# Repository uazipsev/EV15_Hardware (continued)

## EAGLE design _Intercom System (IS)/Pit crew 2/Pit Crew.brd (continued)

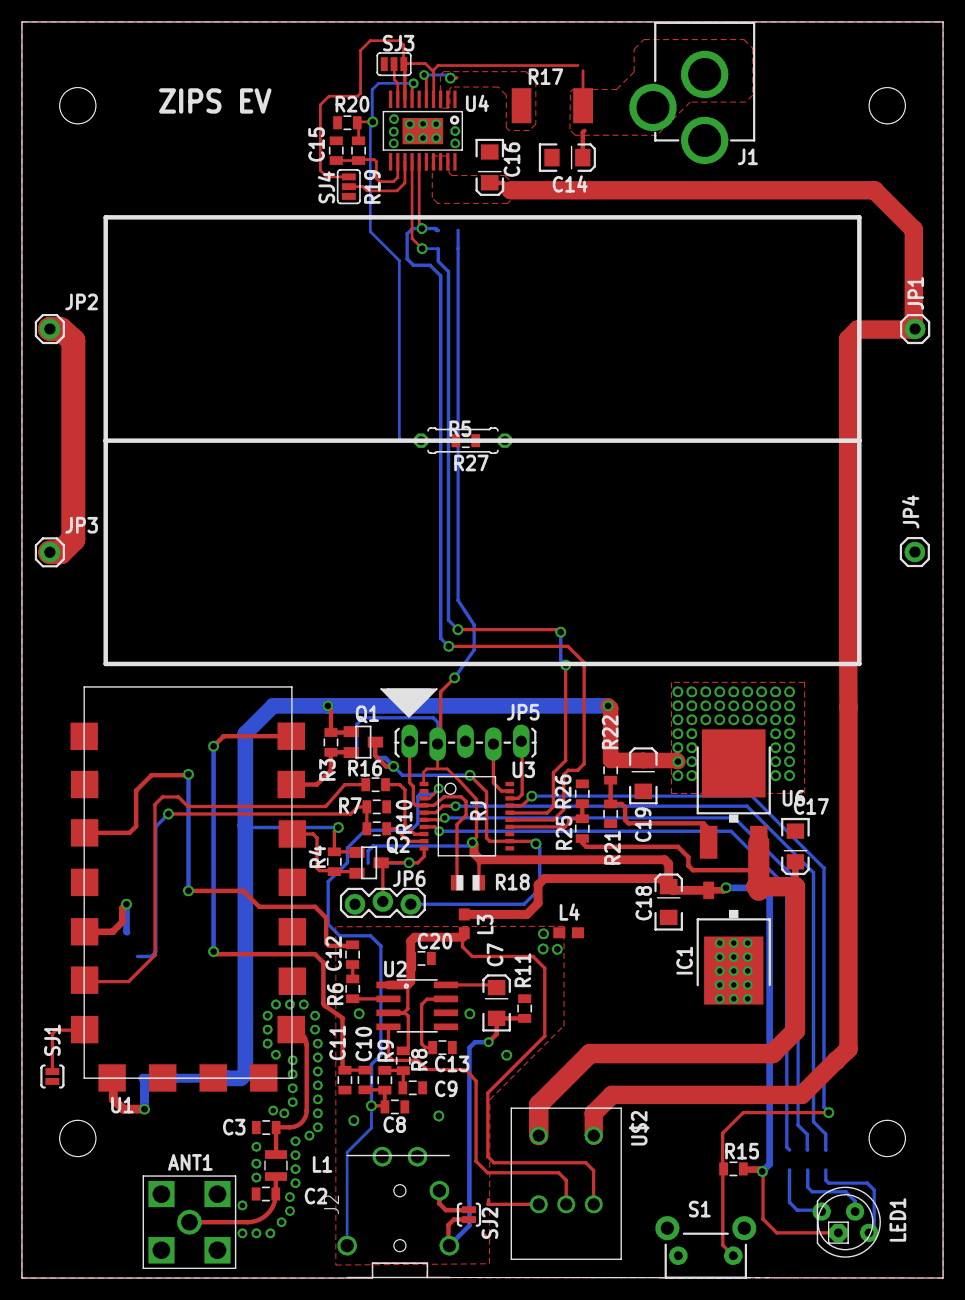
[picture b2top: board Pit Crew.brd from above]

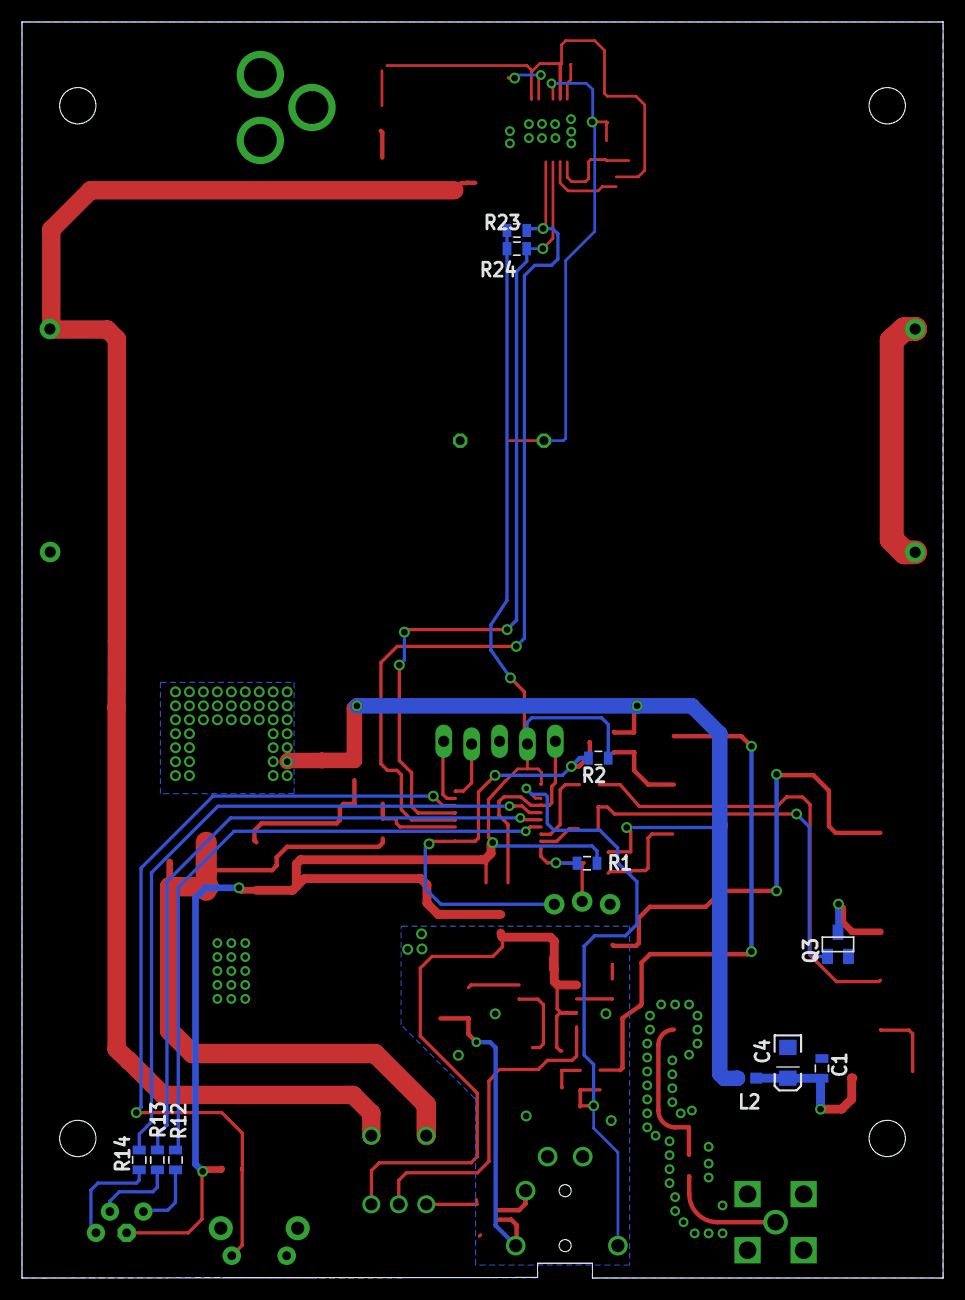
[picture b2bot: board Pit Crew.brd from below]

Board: 2 copper layers, 83.8 x 114.3 mm, 79 parts (11 on the bottom side), 52 nets.

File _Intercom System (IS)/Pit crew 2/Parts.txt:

ANT1	SMA	SMA	CONSMA002	FSAE	2	
C1	100nF	CAP0805	805	SparkFun-Passives	2	
C2	DNC	CAP0805	805	SparkFun-Passives	2	
C3	DNC	CAP0805	805	SparkFun-Passives	2	
C4	100uF	CAP_POL1206	EIA3216	SparkFun-Passives	2	
C5	0.1uf	CAP0805	805	SparkFun-Capacitors	1	
C6	0.1uf	CAP0805	805	SparkFun-Capacitors	1	
C7	10uF	10UF-TANT	EIA3216	SparkFun-Capacitors	2	
C8	470uF	CAP0805	805	SparkFun-Passives	2	
C9	1uF	CAP0805	805	SparkFun-Passives	2	
C10	100nF	CAP0805	805	SparkFun-Passives	2	
C11	100nF	CAP0805	805	SparkFun-Passives	2	
C12	470nF	CAP0805	805	SparkFun-Passives	2	
C13	1uF	CAP0805	805	SparkFun-Passives	2	
C14	10uF	10UF-TANT	EIA3216	SparkFun-Capacitors	1	
C15	0.22uF	CAP0805	805	SparkFun-Passives	1	
C16	1uF	10UF-TANT	EIA3216	SparkFun-Capacitors	1	
C17	10uF	10UF-TANT	EIA3216	SparkFun-Capacitors	1	
C18	10uF	10UF-TANT	EIA3216	SparkFun-Capacitors	1	
C19	10uF	10UF-TANT	EIA3216	SparkFun-Capacitors	1	
C20	0.1uf	CAP0805	805	SparkFun-Passives	2	
IC1	7805	7806DT	TO252	adafruit	1	
J1	POWER_JACKPTH	POWER_JACKPTH	POWER_JACK_PTH	SparkFun-Connectors	1	
JP1	M01PTH	M01PTH	1X01	SparkFun-Connectors	1	
JP2	M01PTH	M01PTH	1X01	SparkFun-Connectors	1	
JP3	M01PTH	M01PTH	1X01	SparkFun-Connectors	1	
JP4	M01PTH	M01PTH	1X01	SparkFun-Connectors	1	
JP5		M05LOCK_LONGPADS	1X05_LOCK_LONGPADS	SparkFun-Connectors	1	
JP6		M03LOCK	1X03_LOCK	SparkFun-Connectors	2	
L1	0	INDUCTOR1007	1007	SparkFun-Passives	2	
L2	BLM18EG221TN1D	INDUCTOR0603	603	SparkFun-Passives	2	
L3	BLM18HG102SN1D	INDUCTOR0603	603	SparkFun-Passives	2	
L4	BLM18HG102SN1D	INDUCTOR0603	603	SparkFun-Passives	2	
LED1	RGBLED_CA-5MM	RGBLED_CA-5MM	LED5MMRGB	adafruit	1	
Q1	BSS123	MOSFET-NCHANNELBSS123LT1G	SOT23	SparkFun-DiscreteSemi	2	
Q2	BSS123	MOSFET-NCHANNELBSS123LT1G	SOT23	SparkFun-DiscreteSemi	2	
Q3	BSS123	MOSFET-NCHANNELBSS123LT1G	SOT23	SparkFun-DiscreteSemi	2	
R1	10k	RESISTOR0805-RES	805	SparkFun-Passives	2	
R2	10k	RESISTOR0805-RES	805	SparkFun-Passives	2	
R3	10k	RESISTOR0805-RES	805	SparkFun-Passives	2	
R4	10k	RESISTOR0805-RES	805	SparkFun-Passives	2	
R5		RESISTOR0805-RES	805	SparkFun-Passives	1	
R6	68k	RESISTOR0805-RES	805	SparkFun-Passives	2	
R7	10k	RESISTOR0805-RES	805	SparkFun-Passives	2	
R8	1k	RESISTOR0805-RES	805	SparkFun-Passives	2	
R9	2.2k	RESISTOR0805-RES	805	SparkFun-Passives	2	
R10	1k	RESISTOR0805-RES	805	SparkFun-Passives	2	
R11	1k	RESISTOR0805-RES	805	SparkFun-Passives	2	
R12		RESISTOR0805-RES	805	SparkFun-Passives	1	
R13		RESISTOR0805-RES	805	SparkFun-Passives	1	
R14		RESISTOR0805-RES	805	SparkFun-Passives	1	
R15	10k	RESISTOR0805-RES	805	SparkFun-Passives	1	
R16	1k	RESISTOR0805-RES	805	SparkFun-Passives	1	
R17	0.2	RESISTOR2512	R2512	SparkFun-Passives	1	
R18	10k	R-US_R0805	R0805	adafruit	1	
R19	10k	RESISTOR0805-RES	805	SparkFun-Passives	1	
R20	10k	RESISTOR0805-RES	805	SparkFun-Passives	1	
R21	620	RESISTOR0805-RES	805	SparkFun-Passives	1	
R22	240	RESISTOR0805-RES	805	SparkFun-Passives	1	
R23	10k	RESISTOR0805-RES	805	SparkFun-Passives	1	
R24	10k	RESISTOR0805-RES	805	SparkFun-Passives	1	
R25	12k	RESISTOR0805-RES	805	SparkFun-Passives	1	
R26	20k	RESISTOR0805-RES	805	SparkFun-Passives	1	
R27		R-US_0207/7	0207/7	adafruit	1	
S1	NO	SWITCH-MOMENTARY-2SIDE_EZ	TACTILE-PTH-SIDEEZ	SparkFun-Electromechanical	1	
SJ1	NO	SOLDERJUMPERNO	SJ_2S-NO	SparkFun-Passives	2	
SJ2	SOLDERJUMPERNO	SJ_2S-NO	SparkFun-Passives	2		
SJ3	SOLDERJUMPER_2WAYS	SJ_3	SparkFun-Passives	1		
SJ4	SOLDERJUMPER_2WAYS	SJ_3	SparkFun-Passives	1		
U$1	AUDIO-JACK3	AUDIO-JACK3	AUDIO-JACK-TRRS-SMD	SparkFun-Connectors	2	
U$2	PTR901-2015K-B103	PTR901-2015K-B103	PTR901-2015K-B103	FSAE	Eletric	2
U1	SR-FRS-1W	SR-FRS-1W	SR-FRS-1W	FSAE	Eletric	2
U2	LM4875MX	LM4875MX	SO-8	FSAE	Eletric	2
U3	PIC16F721	PIC16F721	SSOP-20	FSAE	Eletric	1
U4	BQ24005PWP	BQ24005PWP	HTSSOP-20	FSAE	Eletric	1
U6	AZ1117CD-ADJTRG1	V_REG_317DPACK	V-REG_DPACK	SparkFun-PowerIC	1

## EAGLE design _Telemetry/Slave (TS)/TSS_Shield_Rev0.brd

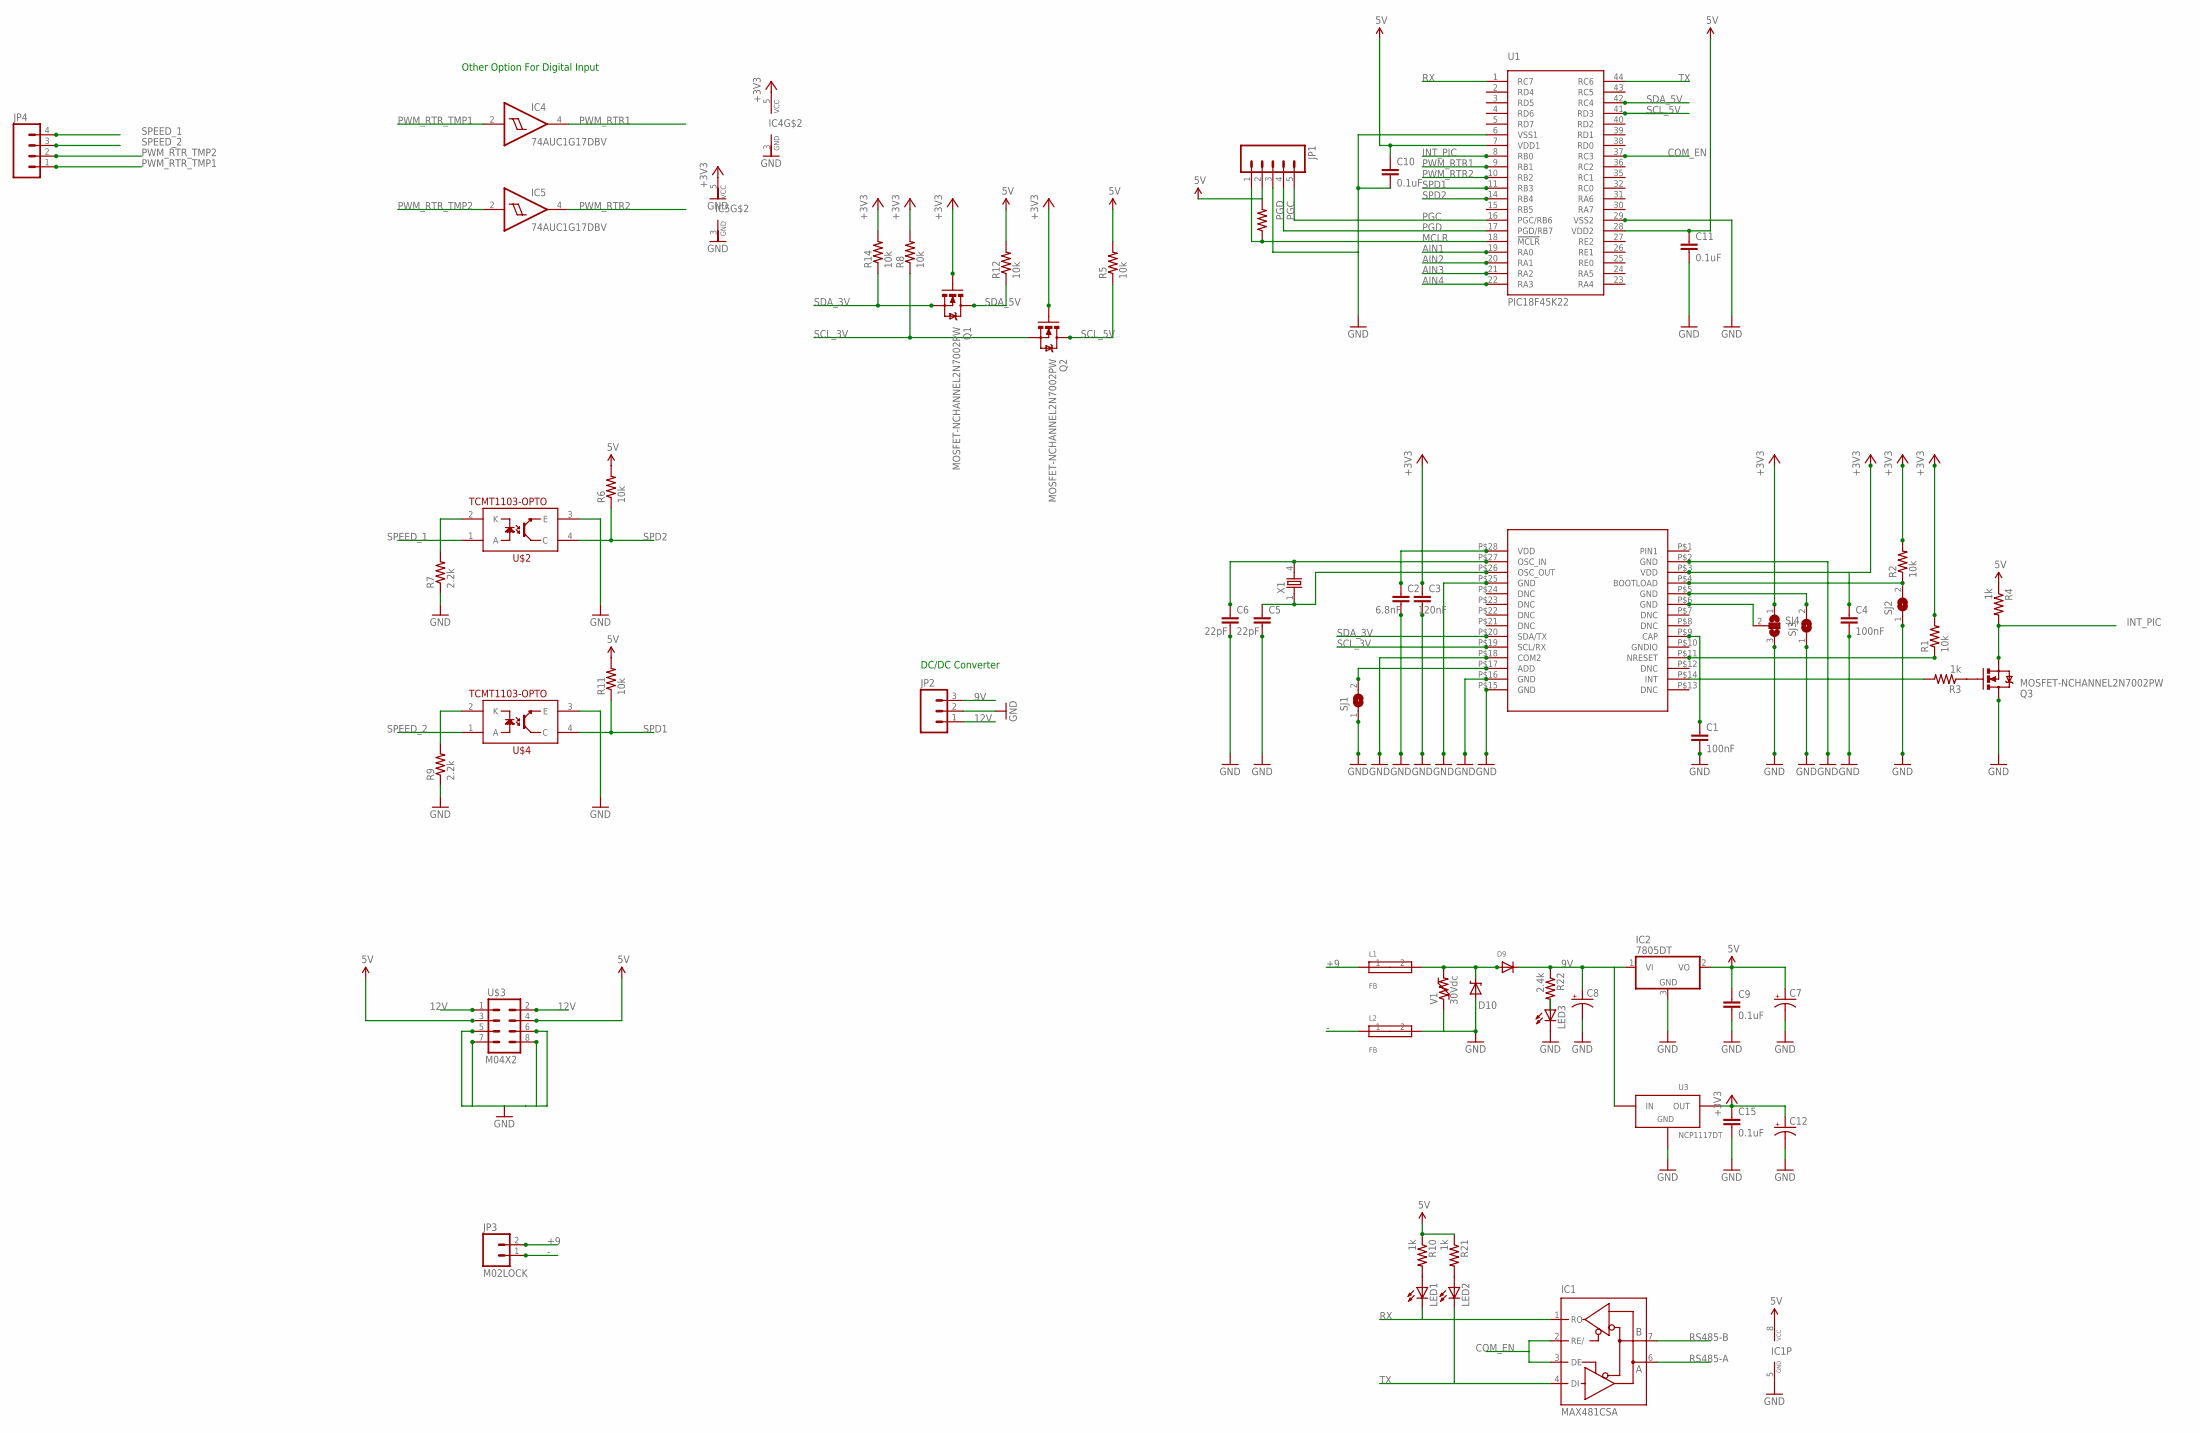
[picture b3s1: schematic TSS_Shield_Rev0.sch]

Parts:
C1, C4: 100nF; 0805
C2: 6.8nF; 0805
C3: 120nF; 0805
C5, C6: 22pF; 0805
C7, C12: CPOL-USCT3528; CT3528
C8: CAP_POL7343; EIA7343
C9, C10, C11, C15: 0.1uF; 0805
D9: DIODESOD-123; SOD-123
D10: MM5Z30; SOD-523F
IC1: MAX481CSA; SO08
IC2: 7805DT; TO252
IC4, IC5: 74AUC1G17DBV; SOT23-5
JP1: M05LOCK; 1X05_LOCK
JP2: M03PTH; 1X03
JP3: M02LOCK; 1X02_LOCK
JP4: M04LOCK; 1X04_LOCK
L1, L2: FB; 0603
LED1, LED2, LED3: LEDCHIP-LED0805; CHIP-LED0805
Q1, Q2, Q3: MOSFET-NCHANNEL2N7002PW; SOT323
R1, R2, R5, R6, R8, R11, R12, R13, R14: 10k; 0805
R3, R4, R10, R21: 1k; 0805
R7, R9: 2.2k; 0805
R22: 2.4k; 0805
SJ1, SJ2, SJ3: SJ
SJ4: SJ2W; SJ_2
U1: PIC18F45K22; TQFP-44
U2: BOSCH_IMUSURFACEMOUNT; LGA_28
U3: NCP1117DT; DPAK
U$2, U$4: TCMT1103-OPTO; SSOP-4
U$3: M04X2; 2X4
V1: 30Vdc; 0603
X1: 86SMX

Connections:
5V: C7.+, C9.1, C10.1, C11.1, IC1.8 (VCC), IC2.2 (VO), JP1.2, R4.1, R5.2, R6.2, R10.1, R11.2, R12.2, R13.2, R21.1, U1.7 (VDD1), U1.28 (VDD2), U$3.3, U$3.4
9V: C8.A (+), D9.C, IC2.1 (VI), JP2.3, R22.1, U3.3 (IN)
12V: JP2.1, U$3.1, U$3.2
+3V3: C2.1, C3.1, C4.1, C12.+, C15.1, IC4.5 (VCC), IC5.5 (VCC), Q1.1 (G), Q2.1 (G), R1.2, R2.2, R8.2, R14.2, SJ4.1, U2.P$3 (VDD), U2.P$28 (VDD), U3.2 (OUT)
+9: JP3.2, L1.1
-: JP3.1, L2.1
AIN1: U1.19 (RA0)
AIN2: U1.20 (RA1)
AIN3: U1.21 (RA2)
AIN4: U1.22 (RA3)
COM_EN: IC1.2 (RE/), IC1.3 (DE), U1.37 (RC3)
GHT: D9.A, D10.C, L1.2, V1.2
GND: C1.2, C2.2, C3.2, C4.2, C5.2, C6.2, C7.-, C8.C (-), C9.2, C10.2, C11.2, C12.-, C15.2, D10.A, IC1.5 (GND), IC2.3 (GND), IC4.3 (GND), IC5.3 (GND), JP1.3, JP2.2, L2.2, LED3.C, Q3.3 (D), R7.1, R9.1, SJ1.1, SJ2.1, SJ3.1, SJ4.3, U1.6 (VSS1), U1.29 (VSS2), U2.P$2 (GND), U2.P$15 (GND), U2.P$16 (GND), U2.P$18 (COM2), U2.P$25 (GND), U3.1 (GND), U$2.3 (E), U$3.5, U$3.6, U$3.7, U$3.8, U$4.3 (E), V1.1
INT_PIC: Q3.2 (S), R4.2, U1.8 (RB0)
MCLR: JP1.1, R13.1, U1.18 (!MCLR)
unnamed: SJ3.2, U2.P$5 (GND)
unnamed: R2.1, SJ2.2, U2.P$4 (BOOTLOAD)
unnamed: SJ4.2, U2.P$6 (GND)
unnamed: LED3.A, R22.2
unnamed: LED1.A, R10.2
unnamed: LED2.A, R21.2
unnamed: C6.1, U2.P$27 (OSC_IN), X1.4 (2)
unnamed: C5.1, U2.P$26 (OSC_OUT), X1.1
unnamed: R7.2, U$2.2 (K)
unnamed: SJ1.2, U2.P$17 (ADD)
unnamed: R9.2, U$4.2 (K)
unnamed: R3.2, U2.P$14 (INT)
unnamed: C1.1, U2.P$9 (CAP)
unnamed: R1.1, U2.P$11 (NRESET)
unnamed: Q3.1 (G), R3.1
PGC: JP1.5, U1.16 (PGC/RB6)
PGD: JP1.4, U1.17 (PGD/RB7)
PWM_RTR1: IC4.4 (O), U1.9 (RB1)
PWM_RTR2: IC5.4 (O), U1.10 (RB2)
PWM_RTR_TMP1: IC4.2 (I), JP4.1
PWM_RTR_TMP2: IC5.2 (I), JP4.2
RS485-A: IC1.6 (A)
RS485-B: IC1.7 (B)
RX: IC1.1 (RO), LED1.C, U1.1 (RC7)
SCL_3V: Q2.2 (S), R8.1, U2.P$19 (SCL/RX)
SCL_5V: Q2.3 (D), R5.1, U1.41 (RD3)
SDA_3V: Q1.2 (S), R14.1, U2.P$20 (SDA/TX)
SDA_5V: Q1.3 (D), R12.1, U1.42 (RC4)
SPD1: R11.1, U1.11 (RB3), U$4.4 (C)
SPD2: R6.1, U1.14 (RB4), U$2.4 (C)
SPEED_1: JP4.4, U$2.1 (A)
SPEED_2: JP4.3, U$4.1 (A)
TX: IC1.4 (DI), LED2.C, U1.44 (RC6)

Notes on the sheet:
DC/DC Converter
Other Option For Digital Input

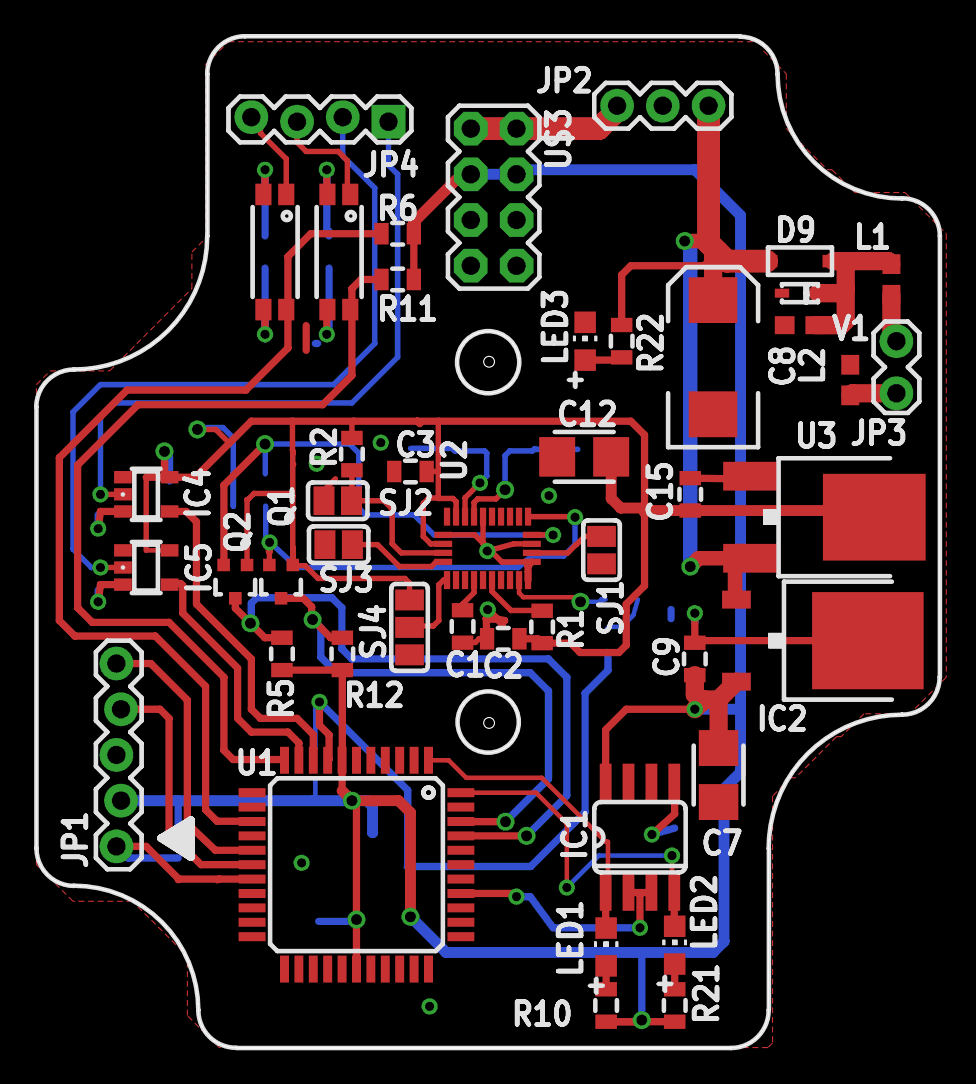
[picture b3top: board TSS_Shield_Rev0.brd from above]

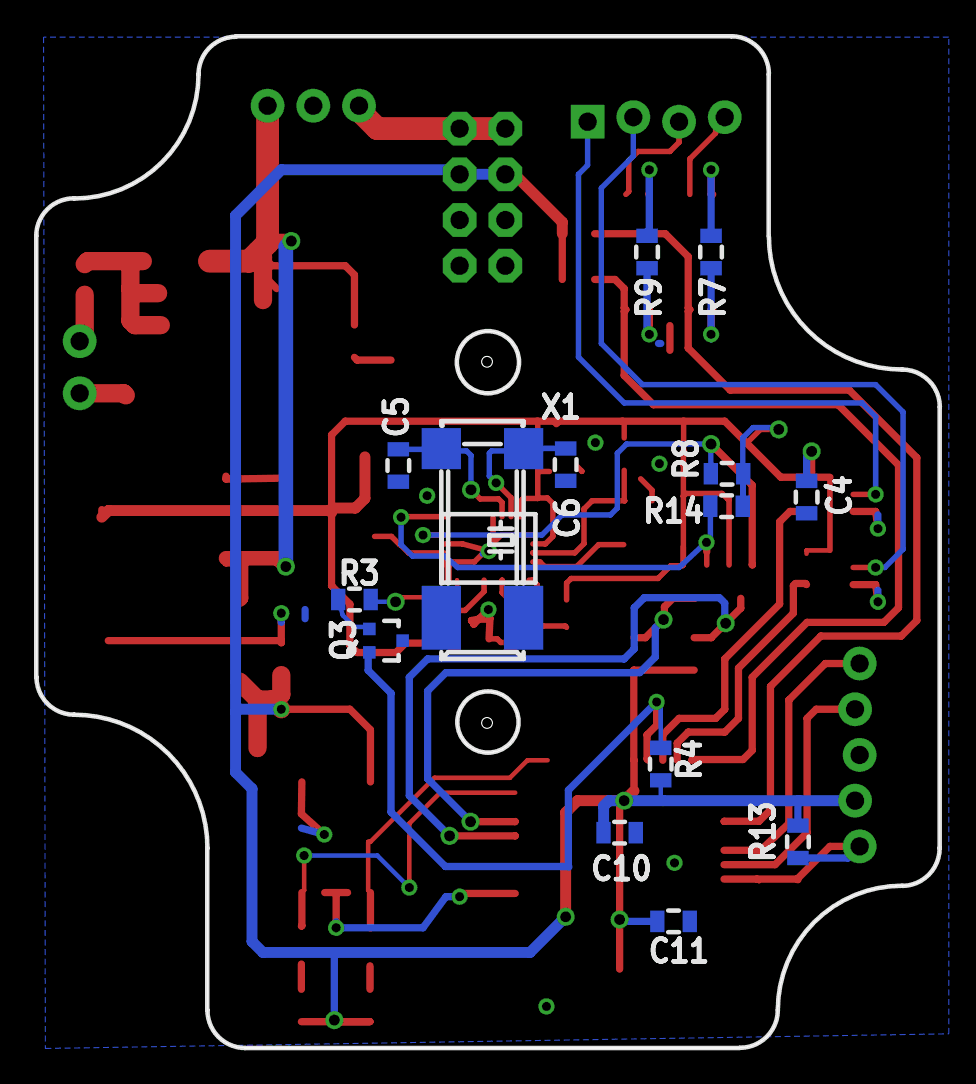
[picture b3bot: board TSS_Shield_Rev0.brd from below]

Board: 2 copper layers, 50.2 x 56.2 mm, 59 parts (14 on the bottom side), 42 nets.

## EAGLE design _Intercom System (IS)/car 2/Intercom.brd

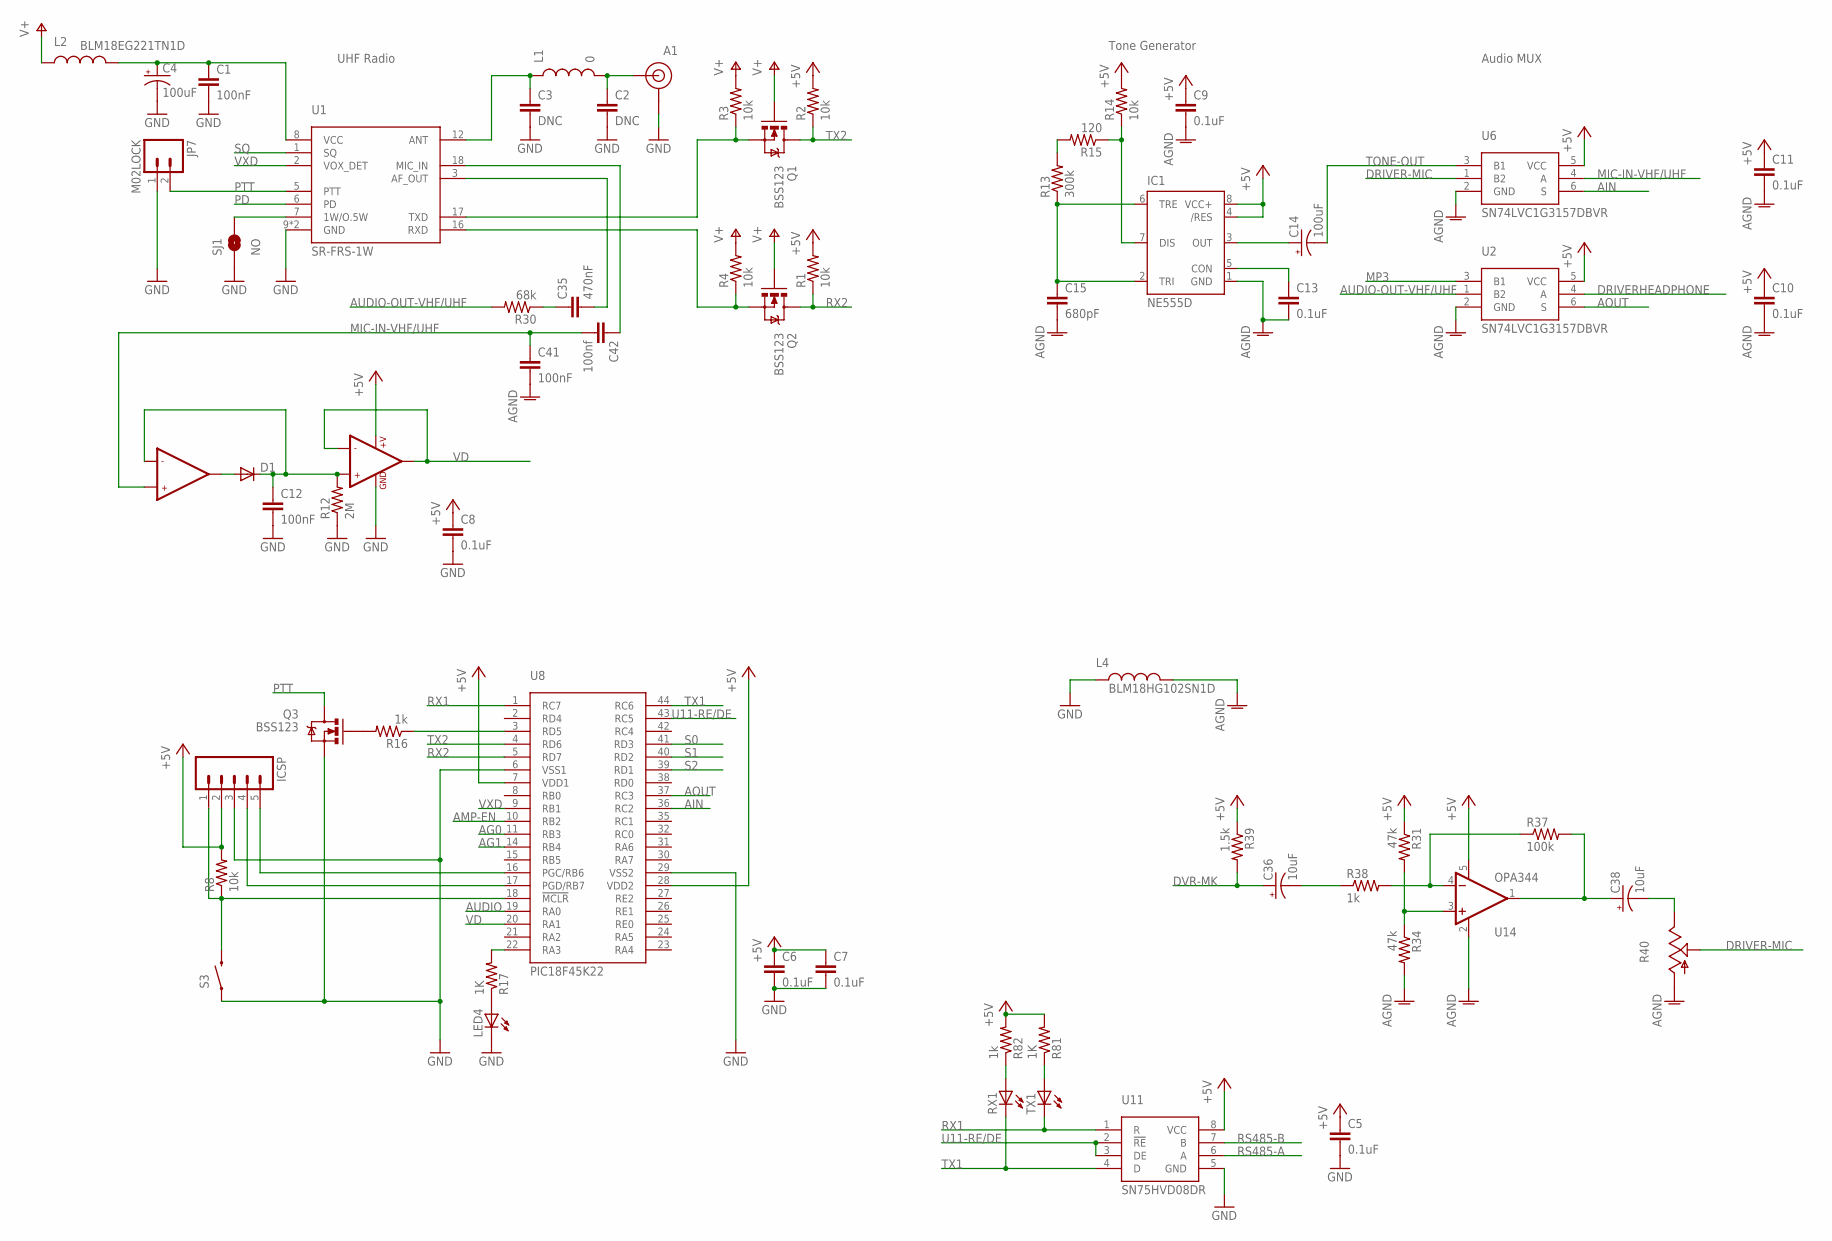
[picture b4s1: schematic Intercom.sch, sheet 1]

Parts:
A1: CONSMA003.062
C1, C12, C41: 100nF; 0805
C2, C3: DNC; 0805
C4: 100uF; EIA3216
C5, C6, C7, C8, C9, C10, C11, C13: 0.1uF; 0805
C14: 100uF; EIA3528-KIT
C15: 680pF; 0805
C35: 470nF; 0805
C36, C38: 10uF; EIA3216
C42: 100nf; 0805
D1: DIODESOD; SOD-323
IC1: NE555D; SO08
ICSP: M05LOCK_LONGPADS; 1X05_LOCK_LONGPADS
JP7: M02LOCK; 1X02_LOCK
L1: 0; 1007
L2: BLM18EG221TN1D; 0603
L4: BLM18HG102SN1D; 0805
LED4: LEDCHIPLED_0805; CHIPLED_0805
Q1, Q2, Q3: BSS123; SOT23
R1, R2, R3, R4, R8, R14: 10k; 0805
R12: 2M; 0805
R13: 300k; 0805
R15: 120; 0805
R16, R38: 1k; 0805
R17, R81: 1K; R0805
R30: 68k; 0805
R31, R34: 47k; 0805
R37: 100k; 0805
R39: 1.5k; 0805
R40: TRIM_US-CA6H; CA6H
R82: 1k; R0805
RX1: LEDCHIPLED_0805; CHIPLED_0805
S3: SWITCH-MOMENTARY-2SIDE_EZ; TACTILE-PTH-SIDEEZ
SJ1: NO; SJ_2S-NO
TX1: LEDCHIPLED_0805; CHIPLED_0805
U1: SR-FRS-1W
U2, U6: SN74LVC1G3157DBVR; SOT23-6
U8: PIC18F45K22; TQFP-44
U11: SN75HVD08DR; SO-8
U12: LMV358; SO08
U14: OPA344; SOT23-5

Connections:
+5V: C5.1, C6.1, C7.1, C8.1, C9.1, C10.1, C11.1, IC1.4 (/RES), IC1.8 (VCC+), ICSP.2, R1.2, R2.2, R8.2, R14.2, R31.1, R39.1, R81.2, R82.2, U2.5 (VCC), U6.5 (VCC), U8.7 (VDD1), U8.28 (VDD2), U11.8 (VCC), U12.8 (+V), U14.5 (V+); also elsewhere on the board
AG0: U8.11 (RB3)
AG1: U8.14 (RB4)
AGND: C9.2, C10.2, C11.2, C13.2, C15.2, C41.2, IC1.1 (GND), L4.2, R34.2, R40.A, U2.2 (GND), U6.2 (GND), U14.2 (V-); also elsewhere on the board
AIN: U6.6 (S), U8.36 (RC2)
AMP-EN: U8.10 (RB2)
AOUT: U2.6 (S), U8.37 (RC3)
AUDIO: U8.19 (RA0)
AUDIO-OUT-VHF/UHF: R30.2, U2.1 (B2)
DRIVER-MIC: R40.S, U6.1 (B2)
DRIVERHEADPHONE: U2.4 (A)
DVR-MK: C36.A (+), R39.2; also elsewhere on the board
GND: A1.G (GND), A1.G1 (GND), A1.G2 (GND), A1.G3 (GND), C1.2, C2.2, C3.2, C4.C (-), C5.2, C6.2, C7.2, C8.2, C12.2, ICSP.3, JP7.1, L4.1, LED4.C, Q3.2 (S), R12.1, S3.1, SJ1.1, U1.9 (GND), U1.10 (GND), U8.6 (VSS1), U8.29 (VSS2), U11.5 (GND), U12.4 (GND); also elsewhere on the board
MIC-IN-VHF/UHF: C41.1, C42.2, U6.4 (A), U12.5 (+IN2)
MP3: U2.3 (B1); also elsewhere on the board
unnamed: C3.1, L1.1, U1.12 (ANT)
unnamed: A1.S (SIGNAL), C2.1, L1.2
unnamed: C1.1, C4.A (+), L2.2, U1.8 (VCC)
unnamed: SJ1.2, U1.7 (1W/O.5W)
unnamed: D1.2 (A), U12.7 (OUT2)
unnamed: C15.1, IC1.2 (TRI), IC1.6 (TRE), R13.1
unnamed: Q2.2 (S), R4.1, U1.16 (RXD)
unnamed: Q1.2 (S), R3.1, U1.17 (TXD)
unnamed: C35.2, U1.3 (AF_OUT)
unnamed: R31.2, R34.1, U14.3 (+IN)
unnamed: C35.1, R30.1
unnamed: R16.1, U8.3 (RD5)
unnamed: C38.C (-), R40.E
unnamed: C12.1, D1.1 (C), R12.2, U12.3 (+IN1), U12.6 (-IN2)
unnamed: IC1.7 (DIS), R14.1, R15.1
unnamed: R13.2, R15.2
unnamed: C13.1, IC1.5 (CON)
unnamed: Q3.1 (G), R16.2
unnamed: C14.A (+), IC1.3 (OUT)
unnamed: LED4.A, R17.1
unnamed: R17.2, U8.22 (RA3)
unnamed: C38.A (+), R37.2, U14.1 (OUT)
unnamed: R37.1, R38.2, U14.4 (-IN)
unnamed: C36.C (-), R38.1
unnamed: ICSP.4, U8.17 (PGD/RB7)
unnamed: ICSP.5, U8.16 (PGC/RB6)
unnamed: ICSP.1, R8.1, S3.2, U8.18 (!MCLR)
unnamed: C42.1, U1.18 (MIC_IN)
unnamed: R81.1, TX1.A
unnamed: R82.1, RX1.A
PD: U1.6 (PD)
PTT: JP7.2, Q3.3 (D), U1.5 (PTT)
RS485-A: U11.6 (A); also elsewhere on the board
RS485-B: U11.7 (B); also elsewhere on the board
RX1: TX1.C, U8.1 (RC7), U11.1 (R)
RX2: Q2.3 (D), R1.1, U8.5 (RD7)
S0: U8.41 (RD3); also elsewhere on the board
S1: U8.40 (RD2); also elsewhere on the board
S2: U8.39 (RD1); also elsewhere on the board
SQ: U1.1 (SQ)
TONE-OUT: C14.C (-), U6.3 (B1)
TX1: RX1.C, U8.44 (RC6), U11.4 (D)
TX2: Q1.3 (D), R2.1, U8.4 (RD6)
U11-RE/DE: U8.43 (RC5), U11.2 (!RE), U11.3 (DE)
V+: L2.1, Q1.1 (G), Q2.1 (G), R3.2, R4.2; also elsewhere on the board
VD: U8.20 (RA1), U12.1 (OUT1), U12.2 (-IN1)
VXD: U1.2 (VOX_DET), U8.9 (RB1)

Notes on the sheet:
UHF Radio
Tone Generator
Audio MUX

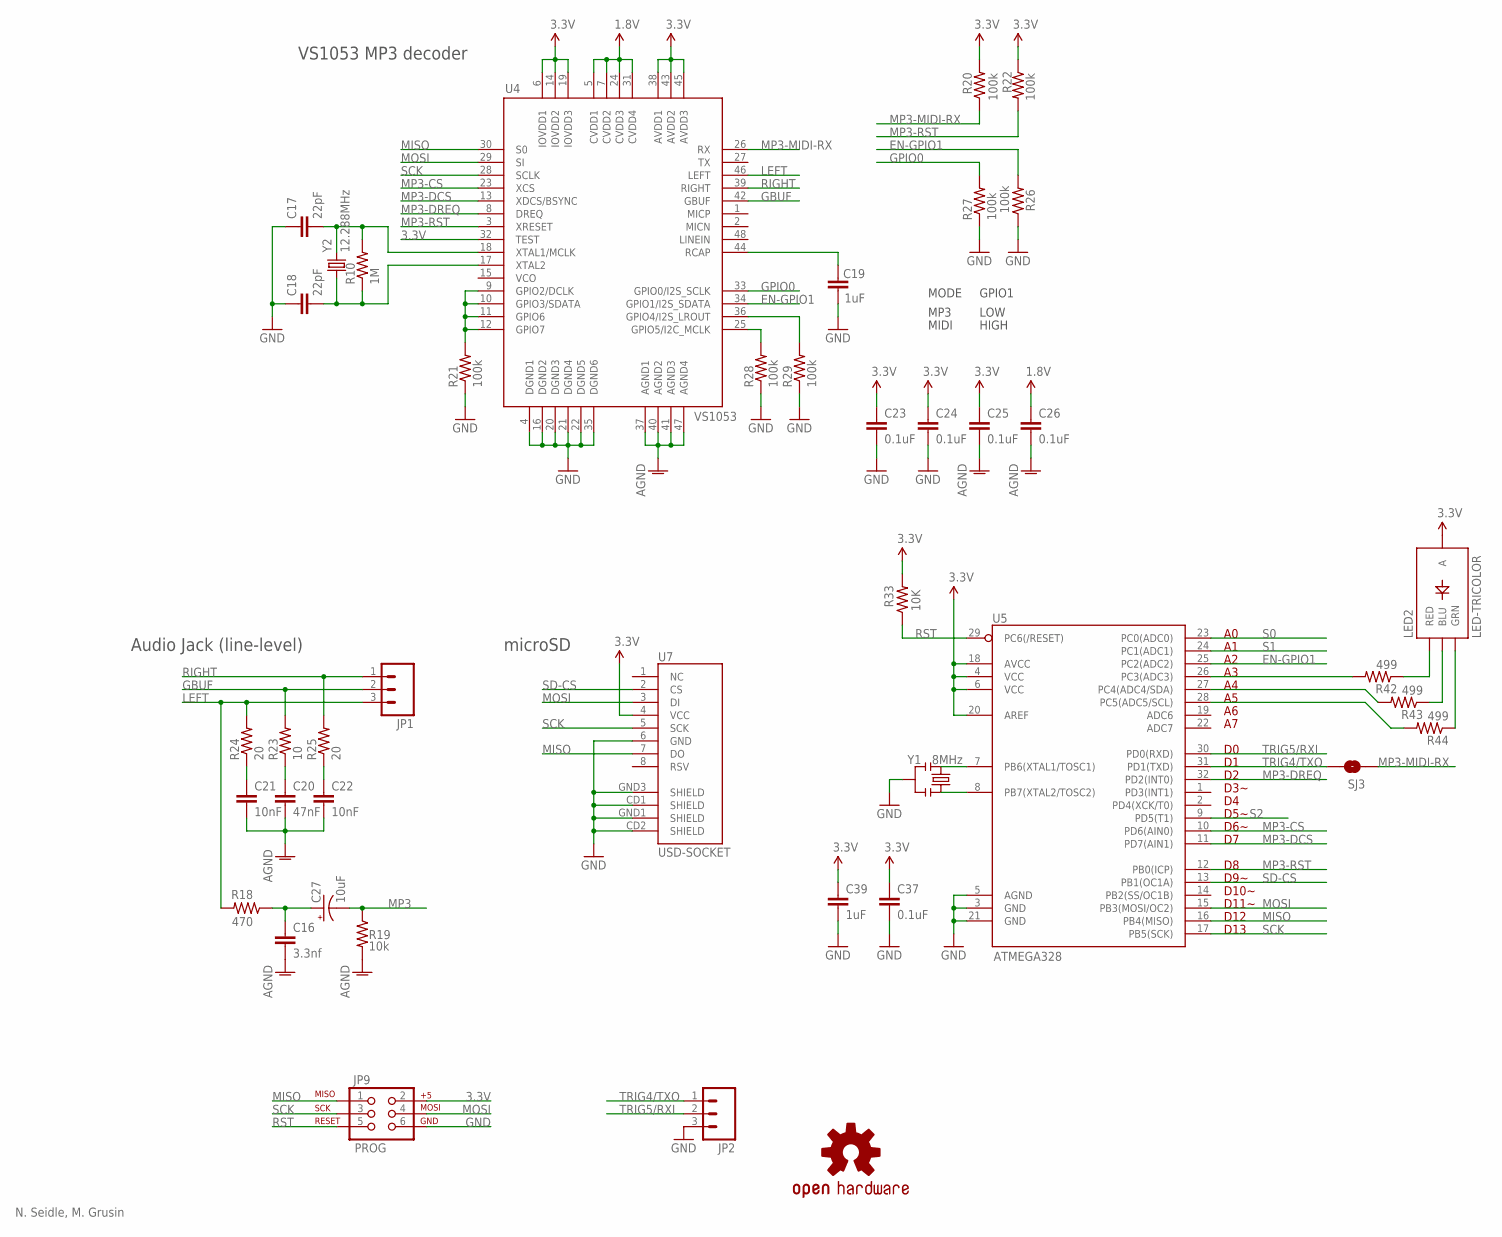
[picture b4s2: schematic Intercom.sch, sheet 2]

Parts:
C16: 3.3nf; 0805
C17, C18: 22pF; 0805
C19, C39: 1uF; 0805
C20: 47nF; 0805
C21, C22: 10nF; 0805
C23, C24, C25, C26, C37: 0.1uF; 0805
C27: 10uF; CT6032
JP1: M03PTH; 1X03
JP2: M03LOCK_LONGPADS; 1X03_LOCK_LONGPADS
JP9: PROG; 2X3-NS
LED2: LED-TRICOLOR; LED-TRICOLOR-SMD
R10: 1M; 0805
R18: 470; 0805
R19: 10k; 0805
R20, R21, R22, R26, R27, R28, R29: 100k; 0805
R23: 10; 0805
R24, R25: 20; 0805
R33: 10K; 0805
R42, R43, R44: 499; 0805
SJ3: SOLDERJUMPERNO; SJ_2S-NO
U4: VS1053; LQFP-48
U5: ATMEGA328; TQFP32-08
U7: USD-SOCKET; MICRO-SD-SOCKET-PP
U$5: OSHW-LOGOM; OSHW-LOGO-M
Y1: 8MHz; RESONATOR-SMD
Y2: 12.288MHz; CRYSTAL-SMD-5X3

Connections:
1.8V: C26.1, U4.5 (CVDD1), U4.7 (CVDD2), U4.24 (CVDD3), U4.31 (CVDD4); also elsewhere on the board
3.3V: C23.1, C24.1, C25.1, C37.1, C39.1, JP9.2, LED2.A, R20.2, R22.1, R33.2, U4.6 (IOVDD1), U4.14 (IOVDD2), U4.19 (IOVDD3), U4.32 (TEST), U4.38 (AVDD1), U4.43 (AVDD2), U4.45 (AVDD3), U5.4 (VCC), U5.6 (VCC), U5.18 (AVCC), U5.20 (AREF), U7.4 (VCC); also elsewhere on the board
AGND: C16.2, C20.2, C21.2, C22.2, C25.2, C26.2, R19.2, U4.37 (AGND1), U4.40 (AGND2), U4.41 (AGND3), U4.47 (AGND4); also elsewhere on the board
EN-GPIO1: R26.2, U4.34 (GPIO1/I2S_SDATA), U5.25 (PC2(ADC2))
G1: R21.2, U4.9 (GPIO2/DCLK), U4.10 (GPIO3/SDATA), U4.11 (GPIO6), U4.12 (GPIO7)
G2: R28.2, U4.25 (GPIO5/I2C_MCLK)
GBUF: JP1.2, R23.2, U4.42 (GBUF)
GND: C17.1, C18.1, C19.1, C23.2, C24.2, C37.2, C39.2, JP2.3, JP9.6, R21.1, R26.1, R27.1, R28.1, R29.1, U4.4 (DGND1), U4.16 (DGND2), U4.20 (DGND3), U4.21 (DGND4), U4.22 (DGND5), U4.35 (DGND6), U5.3 (GND), U5.5 (AGND), U5.21 (GND), U7.6 (GND), U7.CD1 (SHIELD), U7.CD2 (SHIELD), U7.GND1 (SHIELD), U7.GND3 (SHIELD), Y1.2; also elsewhere on the board
GPIO0: R27.2, U4.33 (GPIO0/I2S_SCLK)
LEFT: JP1.3, R18.2, R24.2, U4.46 (LEFT)
MISO: JP9.1, U4.30 (S0), U5.16 (PB4(MISO)), U7.7 (DO)
MOSI: JP9.4, U4.29 (SI), U5.15 (PB3(MOSI/OC2)), U7.3 (DI)
MP3: C27.-, R19.1; also elsewhere on the board
MP3-CS: U4.23 (XCS), U5.10 (PD6(AIN0))
MP3-DCS: U4.13 (XDCS/BSYNC), U5.11 (PD7(AIN1))
MP3-DREQ: U4.8 (DREQ), U5.32 (PD2(INT0))
MP3-MIDI-RX: R20.1, SJ3.1, U4.26 (RX)
MP3-RST: R22.2, U4.3 (XRESET), U5.12 (PB0(ICP))
unnamed: C17.2, R10.2, U4.18 (XTAL1/MCLK), Y2.3 (2)
unnamed: C18.2, R10.1, U4.17 (XTAL2), Y2.1
unnamed: C16.1, C27.+, R18.1
unnamed: C19.2, U4.44 (RCAP)
unnamed: C22.1, R25.1
unnamed: C21.1, R24.1
unnamed: C20.1, R23.1
unnamed: U5.7 (PB6(XTAL1/TOSC1)), Y1.1
unnamed: U5.8 (PB7(XTAL2/TOSC2)), Y1.3
unnamed: LED2.R (RED), R42.1
unnamed: LED2.B (BLU), R43.1
unnamed: LED2.G (GRN), R44.1
unnamed: R42.2, U5.26 (PC3(ADC3))
unnamed: R43.2, U5.27 (PC4(ADC4/SDA))
unnamed: R44.2, U5.28 (PC5(ADC5/SCL))
unnamed: R29.2, U4.36 (GPIO4/I2S_LROUT)
RIGHT: JP1.1, R25.2, U4.39 (RIGHT)
RST: JP9.5, R33.1, U5.29 (PC6(/RESET))
S0: U5.23 (PC0(ADC0)); also elsewhere on the board
S1: U5.24 (PC1(ADC1)); also elsewhere on the board
S2: U5.9 (PD5(T1)); also elsewhere on the board
SCK: JP9.3, U4.28 (SCLK), U5.17 (PB5(SCK)), U7.5 (SCK)
SD-CS: U5.13 (PB1(OC1A)), U7.2 (CS)
TRIG4/TXO: JP2.1, SJ3.2, U5.31 (PD1(TXD))
TRIG5/RXI: JP2.2, U5.30 (PD0(RXD))

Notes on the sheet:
N. Seidle, M. Grusin
microSD
Audio Jack (line-level)
VS1053 MP3 decoder
GPIO1
LOW
HIGH
MODE
MP3
MIDI
D3~
D5~
D6~
D9~
D10~
D11~
D12
D13

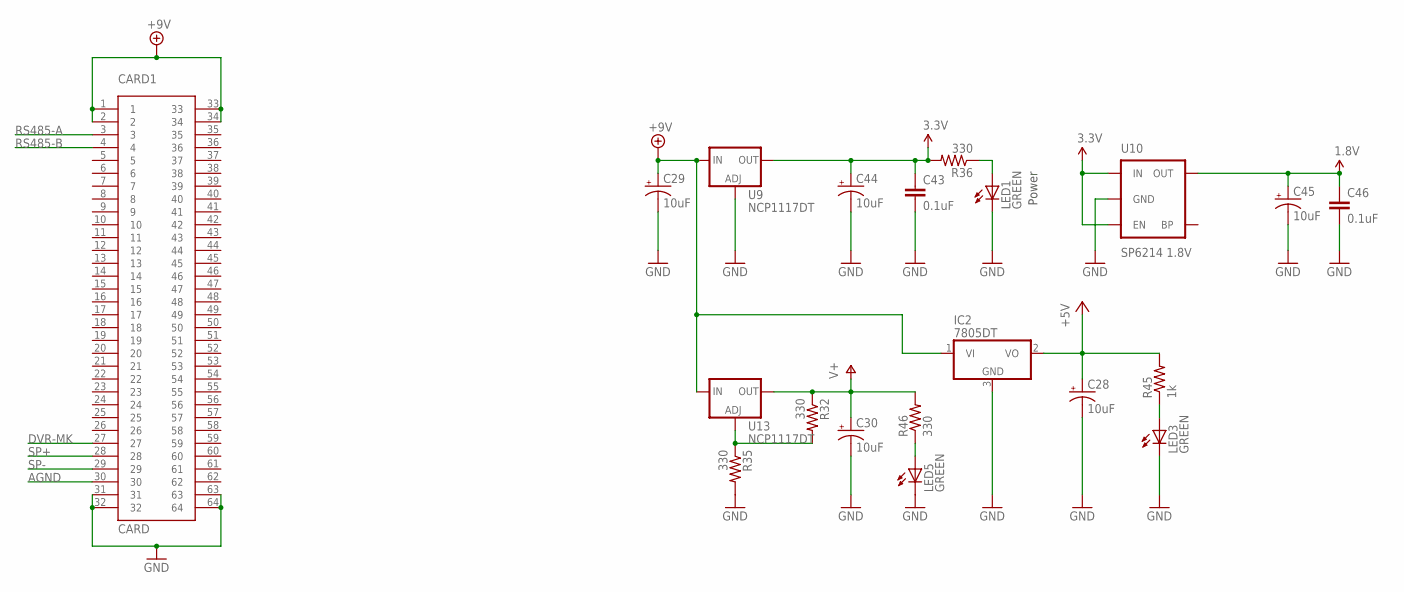
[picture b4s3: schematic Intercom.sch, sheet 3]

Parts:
C28, C30, C44, C45: 10uF; EIA3216
C29: 10uF; EIA7343
C43, C46: 0.1uF; 0805
CARD1: CARD; CARD-64
IC2: 7805DT; TO252
LED1, LED3, LED5: GREEN; CHIPLED_0805
R32, R35, R36, R46: 330; 0805
R45: 1k; 0805
U9, U13: NCP1117DT; V-REG_DPACK
U10: SP6214 1.8V; SC70

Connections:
1.8V: C45.A (+), C46.1, U10.5 (OUT); also elsewhere on the board
3.3V: C43.1, C44.A (+), R36.2, U9.4 (OUT), U10.1 (IN), U10.3 (EN); also elsewhere on the board
+5V: C28.A (+), IC2.2 (VO), R45.2; also elsewhere on the board
+9V: C29.A (+), CARD1.1, CARD1.2, CARD1.33, CARD1.34, IC2.1 (VI), U9.3 (IN), U13.3 (IN)
AGND: CARD1.30; also elsewhere on the board
DVR-MK: CARD1.27; also elsewhere on the board
GND: C28.C (-), C29.C (-), C30.C (-), C43.2, C44.C (-), C45.C (-), C46.2, CARD1.31, CARD1.32, CARD1.63, CARD1.64, IC2.3 (GND), LED1.C, LED3.C, LED5.C, R35.2, U9.1 (ADJ), U10.2 (GND); also elsewhere on the board
unnamed: R32.2, R35.1, U13.1 (ADJ)
unnamed: LED1.A, R36.1
unnamed: LED3.A, R45.1
unnamed: LED5.A, R46.1
RS485-A: CARD1.3; also elsewhere on the board
RS485-B: CARD1.4; also elsewhere on the board
SP+: CARD1.28
SP-: CARD1.29
V+: C30.A (+), R32.1, R46.2, U13.4 (OUT); also elsewhere on the board

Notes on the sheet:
Power
